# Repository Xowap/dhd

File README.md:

# DHD — Dial Hifi Device

<p align="center">
  <strong>A physical motorized fader for seamless computer volume control.</strong>
</p>

<p align="center">
  <a href="https://offworld-nexus-dhd.surge.sh">Documentation</a> ·
  <a href="https://offworld-nexus-dhd.surge.sh/assembly/">Assembly Guide</a> ·
  <a href="https://github.com/Xowap/dhd/tree/develop/hardware/stl">STL Files</a>
</p>

---

Move the fader by hand to adjust volume. Change volume from your computer and
watch the fader glide to match. Bidirectional, seamless, satisfying.

The DHD uses a **Bourns PSL60 motorized fader** with a PID-controlled DC motor,
driven by a **Raspberry Pi Pico 2** and a **DRV8833 motor driver**. The host
daemon on Linux integrates with PulseAudio/PipeWire for system volume control.

The enclosure is designed as a **GEN2 drawer** — it slides directly into the
[GEN2 modular system](https://www.jerrari3d.com/gen2-modular-system) with no
custom fixation needed.

## Features

- **Bidirectional control** — physical fader ↔ software volume, always in sync
- **Auto-calibration** — PID controller tunes itself to your hardware
- **GEN2 compatible** — standard drawer form factor, mounts in seconds
- **Plug and play** — USB auto-discovery, no configuration needed
- **Persistent** — calibration saved to flash, survives reboots

## Quick Start

See the full [documentation](https://offworld-nexus-dhd.surge.sh) for detailed
assembly and installation instructions.

```bash
# Clone
git clone https://github.com/Xowap/dhd.git
cd dhd

# Flash firmware (hold BOOTSEL while plugging in Pico)
rustup target add thumbv8m.main-none-eabihf
cd firmware && cargo run --release && cd ..

# Install host daemon
cd host && cargo run --release -- install && cd ..
```

## Project Structure

```
dhd/
├── common/      # Shared library — protocol + PID controller (no_std)
├── firmware/    # Embassy async firmware for RP2350
├── host/        # Linux host daemon (Tokio + PulseAudio + systray)
├── simulator/   # TUI PID simulator for tuning without hardware
├── hardware/
│   ├── kicad/   # PCB schematics
│   └── stl/     # 3D printable parts
└── doc/         # Documentation source (Zensical)
```

## Documentation

The full documentation is published at
**[offworld-nexus-dhd.surge.sh](https://offworld-nexus-dhd.surge.sh)** and
covers:

- Assembly instructions (BOM, PCB, 3D printing, step-by-step)
- Host software reference (installation, usage, protocol)
- Internals (PID control, motor driver, wiring)

## License

This project is open source. Hardware (KiCad + STL), firmware, and host software
are all available in this repository.

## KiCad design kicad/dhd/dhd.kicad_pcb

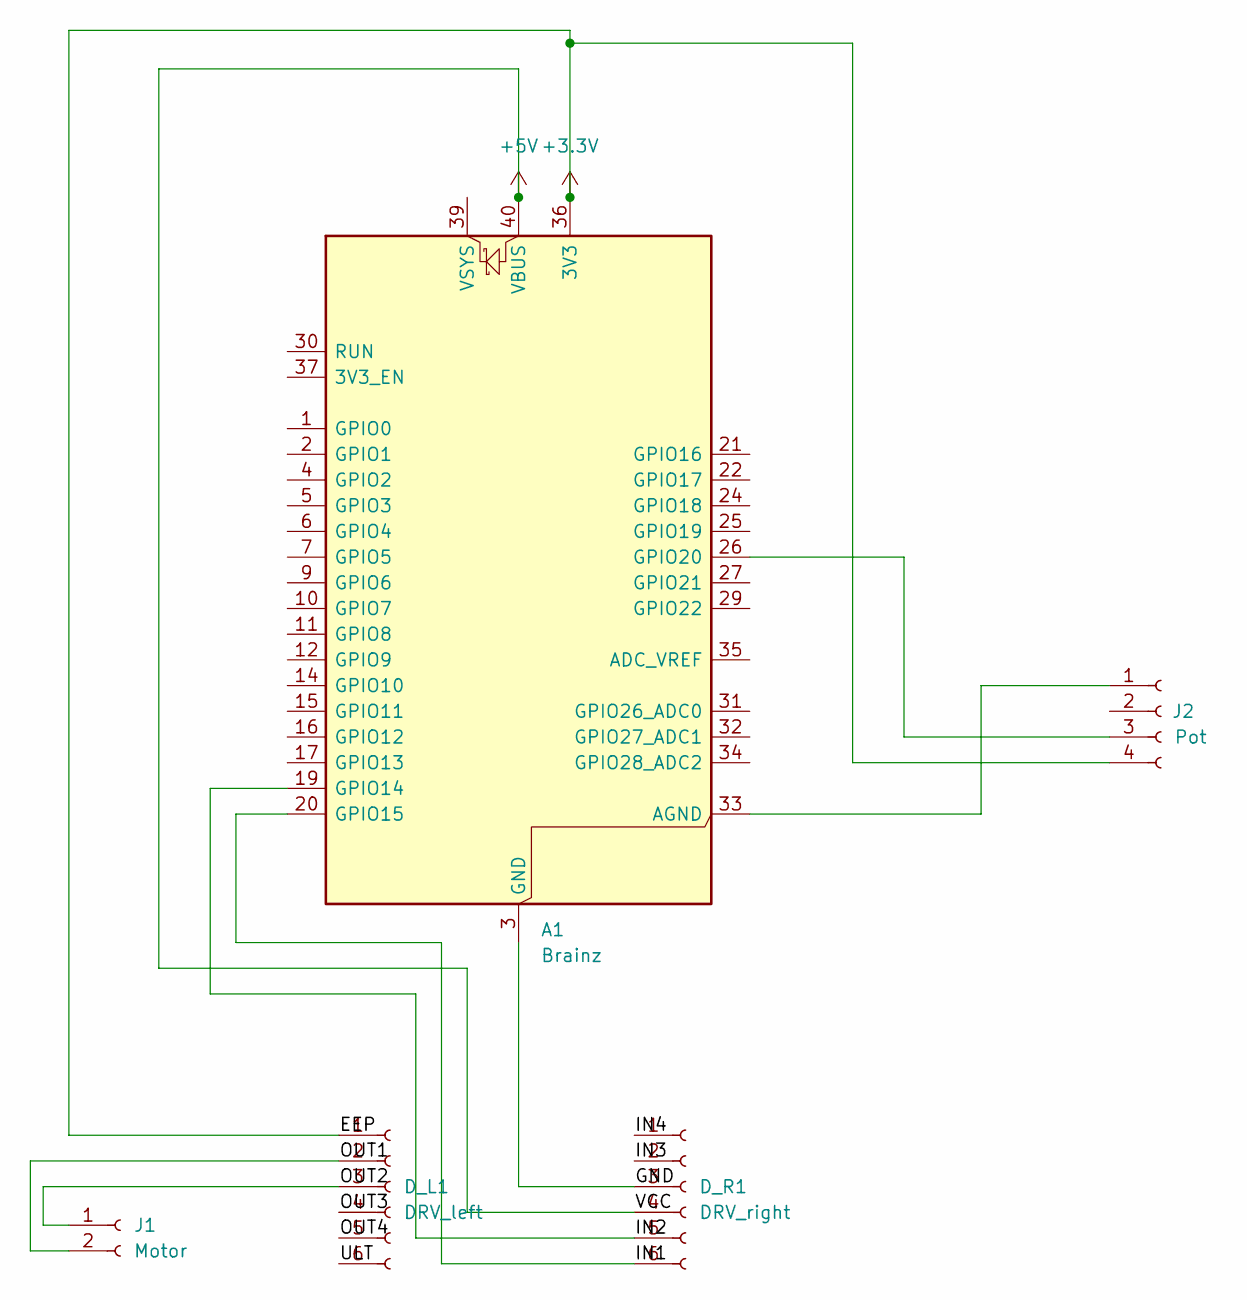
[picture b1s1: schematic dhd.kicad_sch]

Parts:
A1: Brainz; RaspberryPi_Pico_Common_THT
D_L1: DRV_left; PinHeader_1x06_P2.54mm_Vertical
D_R1: DRV_right; PinHeader_1x06_P2.54mm_Vertical
J1: Motor; JST_XH_B2B-XH-A_1x02_P2.50mm_Vertical
J2: Pot; JST_XH_B4B-XH-A_1x04_P2.50mm_Vertical

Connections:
+3.3V: A1.36 (3V3), D_L1.1, J2.4
+5V: A1.40 (VBUS), D_R1.4
/GND: A1.3 (GND), A1.8 (GND), A1.13 (GND), A1.18 (GND), A1.23 (GND), A1.28 (GND), A1.38 (GND), D_R1.3
/IN1: A1.20 (GPIO15), D_R1.6
/IN2: A1.19 (GPIO14), D_R1.5
/IN3: D_R1.2
/IN4: D_R1.1
/OUT1: D_L1.2, J1.2
/OUT2: D_L1.3, J1.1
/OUT3: D_L1.4
/OUT4: D_L1.5
/ULT: D_L1.6
unnamed: A1.33 (AGND), J2.1
unnamed: A1.26 (GPIO20), J2.3

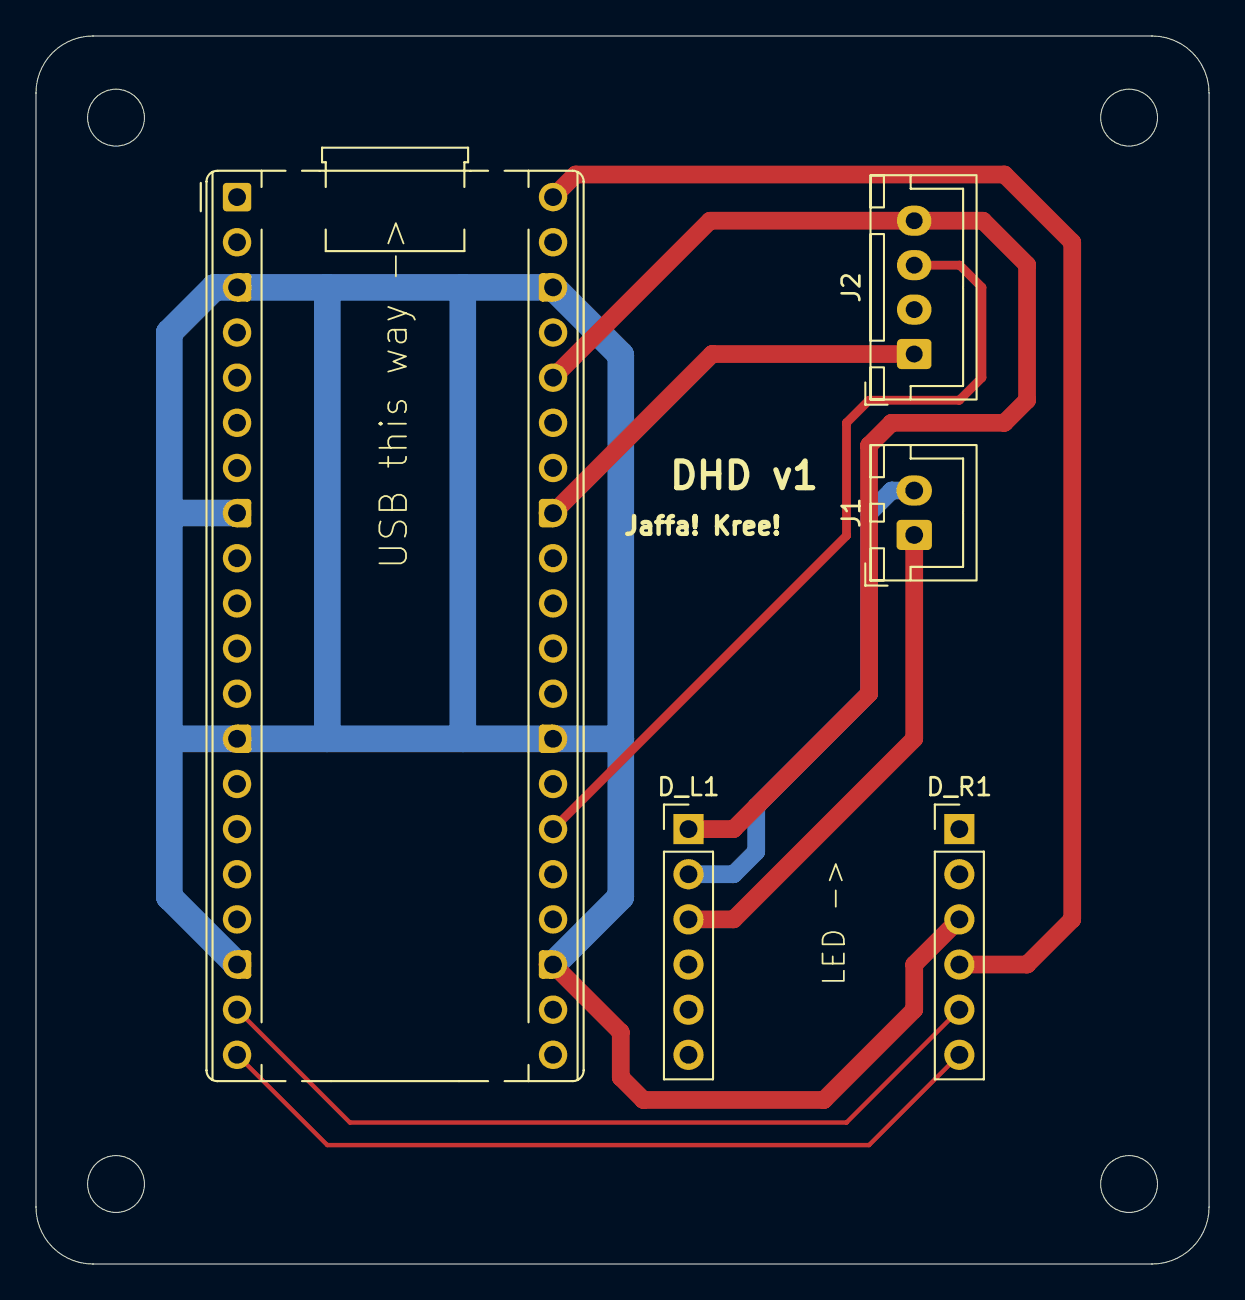
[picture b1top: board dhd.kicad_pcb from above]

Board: 2 copper layers, 66.0 x 69.1 mm, 5 parts (0 on the bottom side), 9 nets.

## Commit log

2026-03-21 Basic blinking project
2026-03-21 Test stuff?
2026-03-21 More complex LED control
2026-03-21 Logging capability
2026-03-21 Refactor using DI principles
2026-03-23 Rename project to "DHD" and implement core functionality for volume control via potentiometer. Replace LED management with volume state management using a DI-based architecture. Update comments and l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
2026-03-23 Adjust USB enumeration delay and refine startup logging procedure
2026-03-23 Add median filtering and hysteresis to PotentiometerManager for smoother volume updates
2026-03-23 Add change notification via Signal to PotentiometerManager and update Monitor to react to value changes
2026-03-26 Host/Firmware architecture
2026-03-26 Documentation
2026-03-26 Add asynchronous PulseAudio support and JSON protocol documentation
    - Implement asynchronous system volume control via PulseAudio integration.
    - Refactor USB communication to utilize `tokio` for non-blocking operations.
    - Add `DHD Protocol Specification` documentation outlining JSON-based communication protocol.
    - Update dependencies to include `tokio`, `libpulse-binding`, `futures`, and related libraries.
2026-03-26 Add handshake mechanism to the DHD protocol for initial connection validation
    - Introduce a JSON-based handshake exchange between host and device.
    - Update host to send and validate handshake messages during connection initialization.
    - Modify firmware to respond to handshake challenges from the host.
    - Adjust ping interval to 1 second and implement a three-ping timeout mechanism for connection monitoring.
    - Update protocol documentation to include handshake and revised ping behavior.
2026-03-27 Implement PulseAudio caching for efficient volume operations
    - Add `PulseCache` struct to store default sink index, channel count, and refresh state.
    - Use subscription to detect default sink changes and update `PulseCache` accordingly.
    - Optimize volume setting by avoiding redundant introspection calls when cached data is valid.
    - Improve logging for default sink changes and apply thread safety with `Arc<Mutex>`.
2026-03-27 Add event-driven PulseAudio notifications and refine logging
    - Introduce `PulseEvent` enum for handling server and sink changes.
    - Implement `tokio::mpsc` channel to process PulseAudio events asynchronously.
    - Replace redundant introspection calls with targeted sink updates on event changes.
    - Consolidate and enhance logging with a reusable `log` helper function.
    - Refactor `PulseController` initialization to return an event receiver channel.
2026-03-27 Make the potentiometer calibrable
2026-03-27 Major refactor and break everything
    The AI is just not managing to go any further on its own. Saving up where we are and going manual
2026-03-28 WIP - Calibration - Finding boundaries
2026-03-28 WIP - Calibration - Low speed finding
2026-04-19 Calibration-driven clipping
2026-04-19 Internal PID controller lib
2026-04-20 Implement run_until_target()
2026-04-20 PID controller real calibration
2026-04-20 Calibration of the physical PID
2026-04-21 Introduce physically and logically driven system modes
    This refactor addresses the need for robust, deterministic, and modular firmware operation without arbitrary delays. The main orchestrator is now split into distinct state handlers, including new `Ph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
    Volume rounding to 1% precision is now applied directly after the filter in the fader task for stability, emitting updates unconditionally. In `PhysicallyDriven` mode, PID resistance is disabled to a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
2026-04-21 [LOG-NONE] Implement persistent calibration storage and host-driven calibration
    This change adds support for storing fader calibration parameters in the RP2350
    flash memory, eliminating the need for a full calibration cycle on every boot.
    A dedicated 4KB .storage section has been carved out in the linker script,
    and a robust storage module with CRC-32 checksums and DMA-aligned buffering
    ensures data integrity.
    The calibration process is now host-driven. Upon connection, the host triggers
2026-04-21 Refactor logging: host-side filtering and firmware verbosity cleanup
    This change moves detailed firmware diagnostic logs (calibration steps,
    flash operations, fader events) from info to debug/trace levels to keep
    the default output clean. The firmware now unconditionally sends all log
    messages to the host, shifting the responsibility of filtering to the
    host tool.
    The host tool has been updated with a new CLI interface using clap,
2026-04-21 Add system tray icon and daemonization support
    The host program now supports a --systray flag which enables a system tray icon and detaches the process from the terminal. The tray icon provides real-time visualization of the device's FSM state us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
    - Added ksni and daemonize dependencies.
    - Implemented tray logic with custom state icons.
    - Added CLI support for daemonization.
    - Updated host logic to communicate state changes to the tray.
2026-04-21 Implement Install Subcommand and Autostart Support
    Refactor the CLI to use clap subcommands, introducing run (default) and install. The install command handles deploying the binary to ~/.local/bin, copying assets to ~/.local/share/dhd, and configurin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
    Additionally, updated the tray icon logic to prioritize the installed asset path and cleaned up CLI type naming from Args to Cli.
2026-04-21 Enhance install command output with colors and emojis
    The install command's output has been updated to be more visually appealing and informative.
    - Added colors (bold, cyan, green, magenta, blue) and emojis to highlight different steps.
    - Improved readability of file paths using italics and dimmed styling.
    - Added a count for the number of assets installed.
    - Improved spacing for better overall terminal presentation.
2026-04-21 Fix dynamic systray updates and enforce singleton daemon lock
    Bypass KDE's theme caching bug by returning absolute file paths to SVGs for the systray icon, enabling immediate visual state changes. The tray now tracks its own state and asynchronously pushes upda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
    A robust file lock (~/.cache/dhd.lock) has been added to guarantee only a single host instance runs at a time. The lock is properly re-acquired post-daemonization to handle closed file descriptors.
    Additionally, the install subcommand output was rewritten to display a cleaner, color-coded directory tree of installed files.
2026-04-21 Update documentation to match current implementation
    Ensure the documentation accurately reflects the current state of the application. The protocol documentation now includes the `mode` and `update_calibration` messages. The wiring documentation has b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
2026-04-21 Embed SVG assets into binary and fix installation file busy error
    Assets are now compiled directly into the binary using the `include_bytes!` macro, eliminating the need for hardcoded development fallback paths and making the executable more self-contained. The ins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
2026-04-25 Add KiCad project files and ignore build artifacts
    Add the initial KiCad project files. Update the .gitignore to exclude KiCad backups, autosaves, locks, and the derived gerbers/ directory to keep the repository clean.
2026-04-25 Submitted KiCad design v1
2026-05-06 Add scale inversion feature to flip volume direction
    Allow inverting the volume scale so that hardware 100% reads as
    volume 0% and vice-versa. This is useful for installations where the
    fader is mounted in reverse orientation.
    The inversion can be toggled from the host via SIGUSR2 or the systray
    "Invert Scale" menu item. The firmware persists the setting in flash
    alongside calibration data, reports it to the host during handshake,
2026-05-10 Construction/assembly guide
2026-05-10 Adding STL files
2026-05-10 Reorganize documentation as a Zensical static site
    Replace the flat collection of markdown files with a structured
    documentation site built on Zensical (Material for MkDocs), managed as
    a uv Python project under doc/.
    Content changes:
    - Split construction.md into dedicated assembly section (BOM, PCB,
    3D printing, step-by-step, GEN2 drawer integration)
2026-05-10 Improve documentation site with proper rendering, navigation, and source links
    Fix several issues with the Zensical-based documentation site that degraded
    the reading experience:
    - Rework zensical.toml markdown extensions to use proper TOML table syntax,
    enabling pymdownx.emoji (with to_svg/twemoji for icon rendering),
    pymdownx.superfences (with mermaid custom fence), pymdownx.arithmatex
    (with MathJax), and navigation.footer for next/prev links
2026-05-10 Fix GitHub links to point to develop instead of master
    All documentation links (blob, tree, raw references) pointed to the
    master branch, which no longer exists. Updated every occurrence across
    the README and all doc pages so that STL downloads, KiCad schematics,
    firmware source links, and code references resolve correctly against
    the actual default branch, develop.
2026-05-10 Clarify Pico 2 compatibility expectations in BOM
    The previous note vaguely said "any Raspberry Pi Pico should do the job"
    while being "totally untested", which was misleading. Replace it with
    specific guidance:
    - Pico 2 (non-W) is the tested target
    - Pico 1 requires a firmware retarget due to the RP2040 vs RP2350 difference
    - Pico 2 W shares the same chip but is untested, with potential USB/power
